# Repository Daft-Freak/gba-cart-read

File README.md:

# GBA Cartridge Reader

Hardware and software for an RP2xxx-based Game Boy and Game Boy Advance cartridge reader that presents the contents as a USB storage device.

## Board
- `board` contains the "v1" PGA2040-based GBA-only board
- `board-v4` contains the new RP2350-based design that also supports Game Boy carts and can _theoretically_ be expanded. (to be added when I make the fixed version)
- (v2/3 designs were never made. For completeness v2 added the Game Boy support, and v3 was a custom RP2040 design)

## Case

- "v1": https://www.printables.com/model/972096-gba-cartridge-reader-case

## Software
For the old RP2040-based boards, just build like any other pico-sdk based project. For the RP2350-based board configure with `cmake -DPICO_BOARD=pico2 -DPICO_RP2350A=0 [...]`.

### Tested GBA carts
 - 8K EEPROM
 - 32k SRAM
 - 64k flash
 - 128k flash

### Tested GB/GBC carts (v4)
 - No MBC
 - MBC1 (<= 512k ROM / 8k RAM)
 - MBC2
 - MBC3
 - MBC5
 - MBC7 (256 byte EEPROM)

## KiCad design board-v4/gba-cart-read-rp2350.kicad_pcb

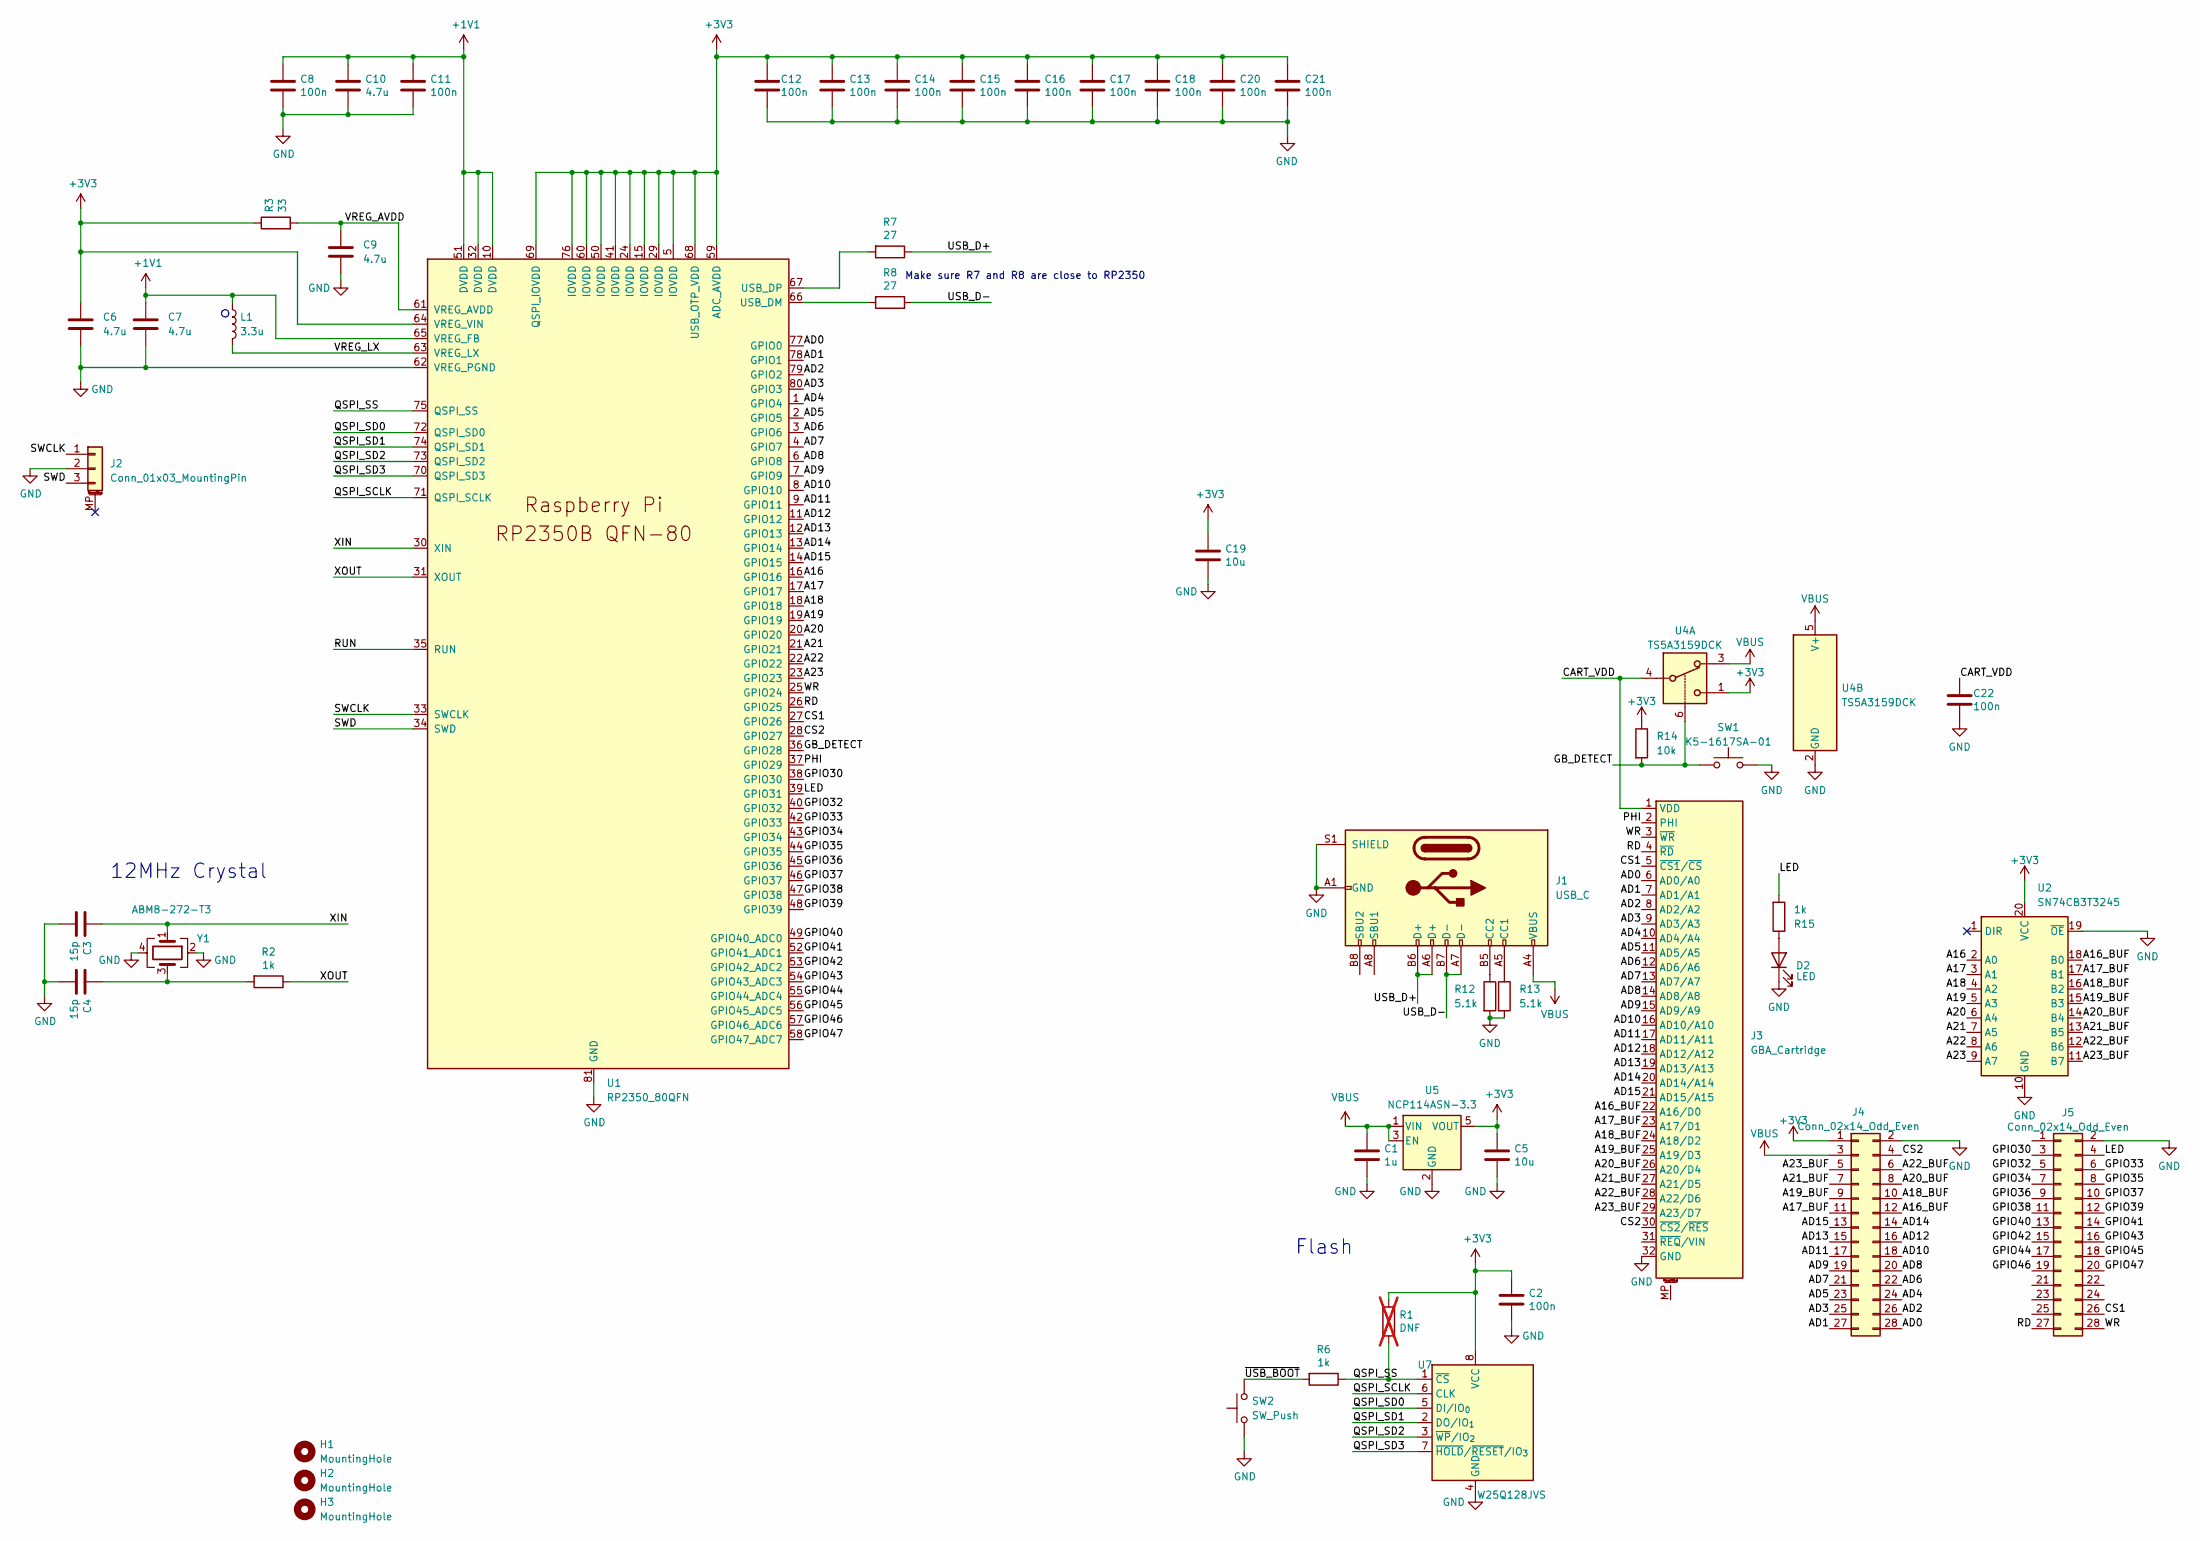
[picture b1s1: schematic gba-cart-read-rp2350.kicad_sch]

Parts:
C1: 1u; C_0805_2012Metric
C2, C8, C11, C12, C13, C14, C15, C16, C17, C18, C20, C21, C22: 100n; C_0402_1005Metric
C3, C4: 15p; C_0402_1005Metric
C5, C19: 10u; C_0805_2012Metric
C6, C7: 4.7u; C_0402_1005Metric_small_pads
C9, C10: 4.7u; C_0402_1005Metric
D2: LED; LED_0603_1608Metric
H1, H2, H3: MountingHole; MountingHole_2.7mm_M2.5
J1: USB_C; USB_C_Receptacle_HRO_TYPE-C-31-M-12
J2: Conn_01x03_MountingPin; JST_SH_SM03B-SRSS-TB_1x03-1MP_P1.00mm_Horizontal
J3: GBA_Cartridge; GameBoy_Cartridge_AGS_1x32-1MP_P1.50mm_Socket_Horizontal
J4, J5: Conn_02x14_Odd_Even; PinHeader_2x14_P2.54mm_Vertical
L1: 3.3u; L_pol_2016
R1: DNF; C_0402_1005Metric; not fitted
R2, R6, R15: 1k; R_0402_1005Metric
R3: 33; R_0402_1005Metric
R7, R8: 27; R_0402_1005Metric
R12, R13: 5.1k; R_0402_1005Metric
R14: 10k; R_0402_1005Metric
SW1: K5-1617SA-01
SW2: SW_Push; SW_Push_1P1T_XKB_TS-1187A
U1: RP2350_80QFN; RP2350-QFN-80-1EP_10x10_P0.4mm_EP3.4x3.4mm_ThermalVias
U2: SN74CB3T3245; TSSOP-20_4.4x6.5mm_P0.65mm
U4: TS5A3159DCK; SOT-363_SC-70-6
U5: NCP114ASN-3.3; TSOP-5_1.65x3.05mm_P0.95mm
U7: W25Q128JVS; SOIC-8_5.3x5.3mm_P1.27mm
Y1: ABM8-272-T3; Crystal_SMD_3225-4Pin_3.2x2.5mm

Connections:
+1V1: C7.1, C8.1, C10.1, C11.1, L1.1, U1.10 (DVDD), U1.32 (DVDD), U1.51 (DVDD), U1.65 (VREG_FB)
+3V3: C2.1, C5.1, C6.1, C12.1, C13.1, C14.1, C15.1, C16.1, C17.1, C18.1, C19.1, C20.1, C21.1, J4.1, R1.1, R3.1, R14.1, U1.5 (IOVDD), U1.15 (IOVDD), U1.24 (IOVDD), U1.29 (IOVDD), U1.41 (IOVDD), U1.50 (IOVDD), U1.59 (ADC_AVDD), U1.60 (IOVDD), U1.64 (VREG_VIN), U1.68 (USB_OTP_VDD), U1.69 (QSPI_IOVDD), U1.76 (IOVDD), U2.20 (VCC), U4.1, U5.5 (VOUT), U7.8 (VCC)
/A16: U1.16 (GPIO16), U2.2 (A0)
/A16_BUF: J3.22 (A16/D0), J4.12, U2.18 (B0)
/A17: U1.17 (GPIO17), U2.3 (A1)
/A17_BUF: J3.23 (A17/D1), J4.11, U2.17 (B1)
/A18: U1.18 (GPIO18), U2.4 (A2)
/A18_BUF: J3.24 (A18/D2), J4.10, U2.16 (B2)
/A19: U1.19 (GPIO19), U2.5 (A3)
/A19_BUF: J3.25 (A19/D3), J4.9, U2.15 (B3)
/A20: U1.20 (GPIO20), U2.6 (A4)
/A20_BUF: J3.26 (A20/D4), J4.8, U2.14 (B4)
/A21: U1.21 (GPIO21), U2.7 (A5)
/A21_BUF: J3.27 (A21/D5), J4.7, U2.13 (B5)
/A22: U1.22 (GPIO22), U2.8 (A6)
/A22_BUF: J3.28 (A22/D6), J4.6, U2.12 (B6)
/A23: U1.23 (GPIO23), U2.9 (A7)
/A23_BUF: J3.29 (A23/D7), J4.5, U2.11 (B7)
/AD0: J3.6 (AD0/A0), J4.28, U1.77 (GPIO0)
/AD1: J3.7 (AD1/A1), J4.27, U1.78 (GPIO1)
/AD2: J3.8 (AD2/A2), J4.26, U1.79 (GPIO2)
/AD3: J3.9 (AD3/A3), J4.25, U1.80 (GPIO3)
/AD4: J3.10 (AD4/A4), J4.24, U1.1 (GPIO4)
/AD5: J3.11 (AD5/A5), J4.23, U1.2 (GPIO5)
/AD6: J3.12 (AD6/A6), J4.22, U1.3 (GPIO6)
/AD7: J3.13 (AD7/A7), J4.21, U1.4 (GPIO7)
/AD8: J3.14 (AD8/A8), J4.20, U1.6 (GPIO8)
/AD9: J3.15 (AD9/A9), J4.19, U1.7 (GPIO9)
/AD10: J3.16 (AD10/A10), J4.18, U1.8 (GPIO10)
/AD11: J3.17 (AD11/A11), J4.17, U1.9 (GPIO11)
/AD12: J3.18 (AD12/A12), J4.16, U1.11 (GPIO12)
/AD13: J3.19 (AD13/A13), J4.15, U1.12 (GPIO13)
/AD14: J3.20 (AD14/A14), J4.14, U1.13 (GPIO14)
/AD15: J3.21 (AD15/A15), J4.13, U1.14 (GPIO15)
/CART_VDD: C22.1, J3.1 (VDD), U4.4
/CS1: J3.5 (~CS1/~CS), J5.26, U1.27 (GPIO26)
/CS2: J3.30 (~CS2/~RES), J4.4, U1.28 (GPIO27)
/GB_DETECT: R14.2, SW1.2, U1.36 (GPIO28), U4.6
/GPIO30: J5.3, U1.38 (GPIO30)
/GPIO32: J5.5, U1.40 (GPIO32)
/GPIO33: J5.6, U1.42 (GPIO33)
/GPIO34: J5.7, U1.43 (GPIO34)
/GPIO35: J5.8, U1.44 (GPIO35)
/GPIO36: J5.9, U1.45 (GPIO36)
/GPIO37: J5.10, U1.46 (GPIO37)
/GPIO38: J5.11, U1.47 (GPIO38)
/GPIO39: J5.12, U1.48 (GPIO39)
/GPIO40: J5.13, U1.49 (GPIO40_ADC0)
/GPIO41: J5.14, U1.52 (GPIO41_ADC1)
/GPIO42: J5.15, U1.53 (GPIO42_ADC2)
/GPIO43: J5.16, U1.54 (GPIO43_ADC3)
/GPIO44: J5.17, U1.55 (GPIO44_ADC4)
/GPIO45: J5.18, U1.56 (GPIO45_ADC5)
/GPIO46: J5.19, U1.57 (GPIO46_ADC6)
/GPIO47: J5.20, U1.58 (GPIO47_ADC7)
/LED: J5.4, R15.2, U1.39 (GPIO31)
/PHI: J3.2 (PHI), U1.37 (GPIO29)
/QSPI_SCLK: U1.71 (QSPI_SCLK), U7.6 (CLK)
/QSPI_SD0: U1.72 (QSPI_SD0), U7.5 (DI/IO_{0})
/QSPI_SD1: U1.74 (QSPI_SD1), U7.2 (DO/IO_{1})
/QSPI_SD2: U1.73 (QSPI_SD2), U7.3 (~WP/IO_{2})
/QSPI_SD3: U1.70 (QSPI_SD3), U7.7 (~HOLD/~RESET/IO_{3})
/QSPI_SS: R1.2, R6.1, U1.75 (QSPI_SS), U7.1 (~CS)
/RD: J3.4 (~RD), J5.27, U1.26 (GPIO25)
/RUN: U1.35 (RUN)
/SWCLK: J2.1, U1.33 (SWCLK)
/SWD: J2.3, U1.34 (SWD)
/USB_D+: J1.A6 (D+), J1.B6 (D+), R7.1
/USB_D-: J1.A7 (D-), J1.B7 (D-), R8.1
/VREG_AVDD: C9.1, R3.2, U1.61 (VREG_AVDD)
/VREG_LX: L1.2, U1.63 (VREG_LX)
/WR: J3.3 (~WR), J5.28, U1.25 (GPIO24)
/XIN: C3.1, U1.30 (XIN), Y1.1
/XOUT: R2.1, U1.31 (XOUT)
/~USB_BOOT: R6.2, SW2.2
GND: C1.2, C2.2, C3.2, C4.2, C5.2, C6.2, C7.2, C8.2, C9.2, C10.2, C11.2, C12.2, C13.2, C14.2, C15.2, C16.2, C17.2, C18.2, C19.2, C20.2, C21.2, C22.2, D2.1 (K), J1.A1 (GND), J1.A12 (GND), J1.B1 (GND), J1.B12 (GND), J1.S1 (SHIELD), J2.2, J3.32 (GND), J4.2, J5.2, R12.2, R13.2, SW1.1, SW2.1, U1.62 (VREG_PGND), U1.81 (GND), U2.10 (GND), U2.19 (~OE), U4.2 (GND), U5.2 (GND), U7.4 (GND), Y1.2, Y1.4
unnamed: C4.1, R2.2, Y1.3
unnamed: D2.2 (A), R15.1
unnamed: J1.A5 (CC1), R13.1
unnamed: J1.B5 (CC2), R12.1
unnamed: R8.2, U1.66 (USB_DM)
unnamed: R7.2, U1.67 (USB_DP)
VBUS: C1.1, J1.A4 (VBUS), J1.A9 (VBUS), J1.B4 (VBUS), J1.B9 (VBUS), J4.3, U4.3, U4.5 (V+), U5.1 (VIN), U5.3 (EN)

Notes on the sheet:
12MHz Crystal
Flash
Make sure R7 and R8 are close to RP2350

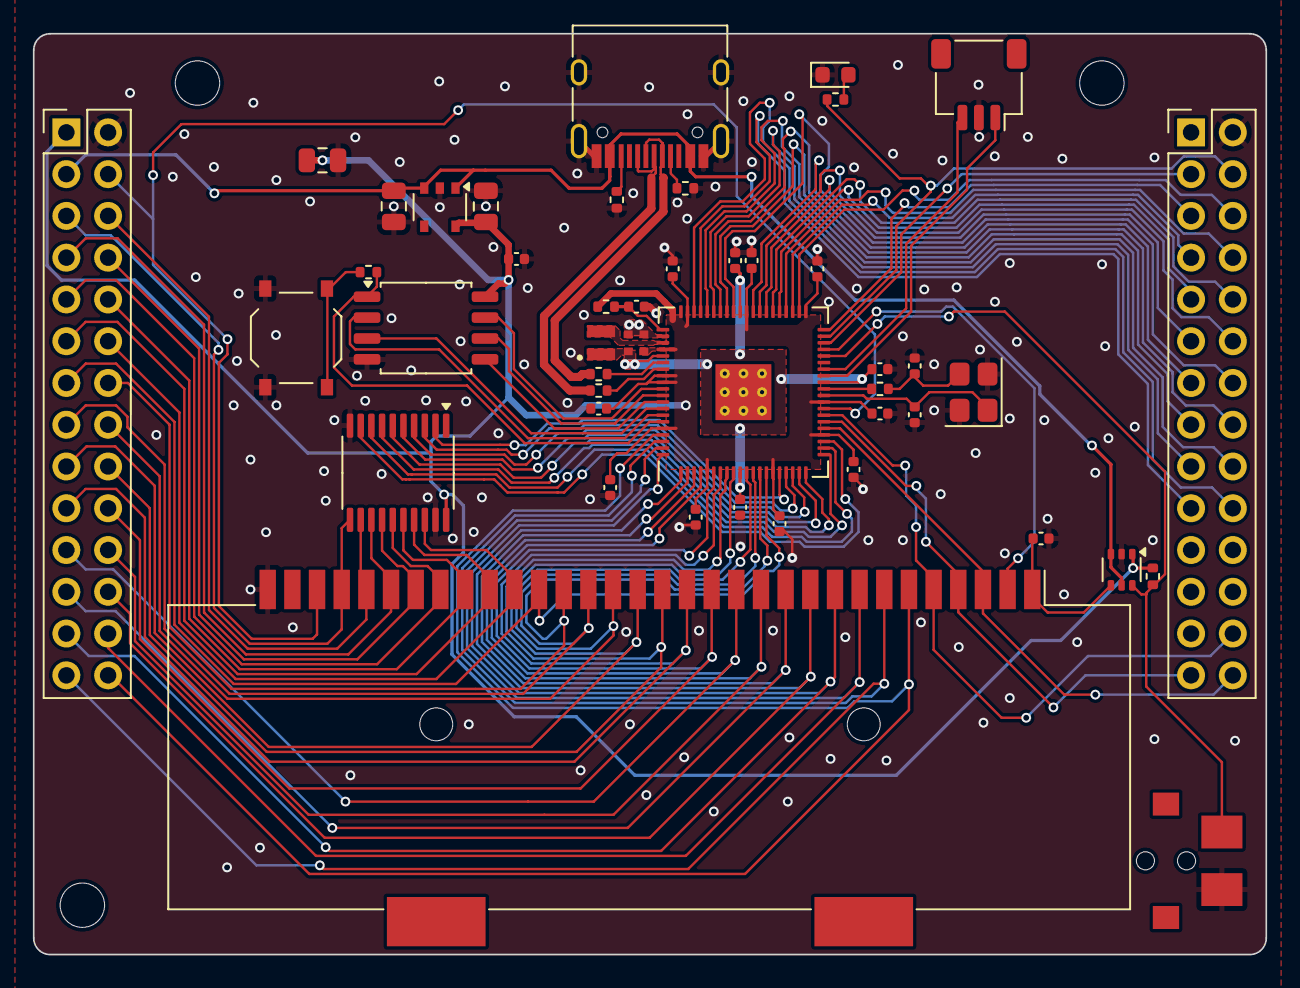
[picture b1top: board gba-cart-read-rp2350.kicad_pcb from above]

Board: 2 copper layers, 75.0 x 56.0 mm, 49 parts (0 on the bottom side), 82 nets.

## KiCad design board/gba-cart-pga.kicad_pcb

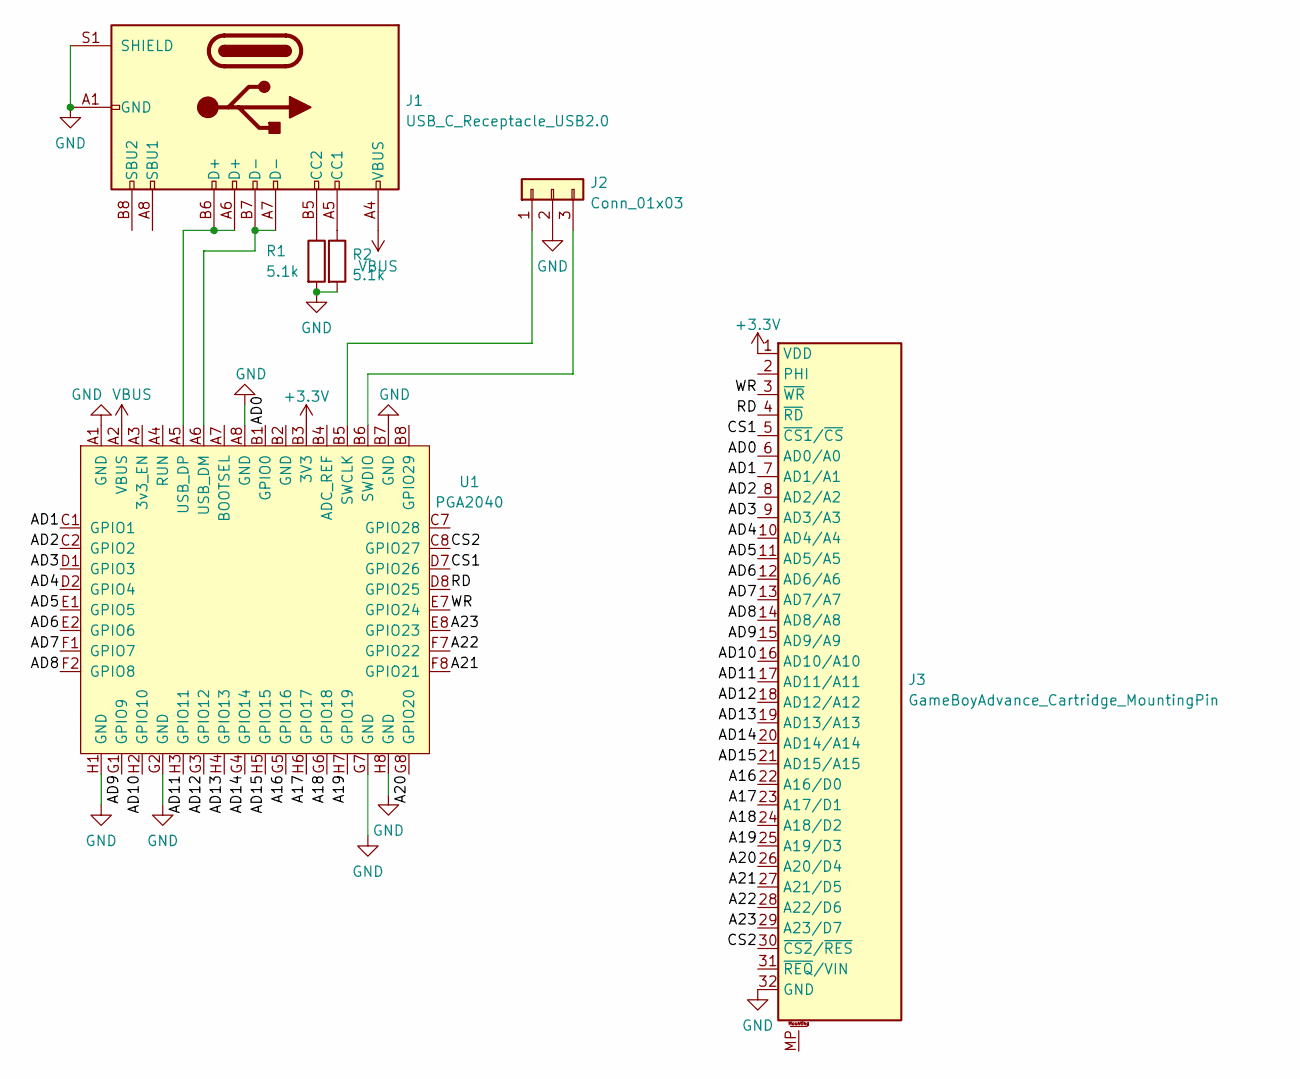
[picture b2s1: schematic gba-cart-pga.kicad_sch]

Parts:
J1: USB_C_Receptacle_USB2.0; USB_C_Receptacle_XKB_U262-16XN-4BVC11
J2: Conn_01x03; PinHeader_1x03_P2.54mm_Vertical
J3: GameBoyAdvance_Cartridge_MountingPin; GameBoy_Cartridge_AGS_1x32-1MP_P1.50mm_Socket_Horizontal
R1, R2: 5.1k; R_0805_2012Metric_Pad1.20x1.40mm_HandSolder
U1: PGA2040; PGA2040_PTH_NO_SLOT

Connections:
+3V3: J3.1 (VDD), U1.B3 (3V3)
/A16: J3.22 (A16/D0), U1.G5 (GPIO16)
/A17: J3.23 (A17/D1), U1.H6 (GPIO17)
/A18: J3.24 (A18/D2), U1.G6 (GPIO18)
/A19: J3.25 (A19/D3), U1.H7 (GPIO19)
/A20: J3.26 (A20/D4), U1.G8 (GPIO20)
/A21: J3.27 (A21/D5), U1.F8 (GPIO21)
/A22: J3.28 (A22/D6), U1.F7 (GPIO22)
/A23: J3.29 (A23/D7), U1.E8 (GPIO23)
/AD0: J3.6 (AD0/A0), U1.B1 (GPIO0)
/AD1: J3.7 (AD1/A1), U1.C1 (GPIO1)
/AD2: J3.8 (AD2/A2), U1.C2 (GPIO2)
/AD3: J3.9 (AD3/A3), U1.D1 (GPIO3)
/AD4: J3.10 (AD4/A4), U1.D2 (GPIO4)
/AD5: J3.11 (AD5/A5), U1.E1 (GPIO5)
/AD6: J3.12 (AD6/A6), U1.E2 (GPIO6)
/AD7: J3.13 (AD7/A7), U1.F1 (GPIO7)
/AD8: J3.14 (AD8/A8), U1.F2 (GPIO8)
/AD9: J3.15 (AD9/A9), U1.G1 (GPIO9)
/AD10: J3.16 (AD10/A10), U1.H2 (GPIO10)
/AD11: J3.17 (AD11/A11), U1.H3 (GPIO11)
/AD12: J3.18 (AD12/A12), U1.G3 (GPIO12)
/AD13: J3.19 (AD13/A13), U1.H4 (GPIO13)
/AD14: J3.20 (AD14/A14), U1.G4 (GPIO14)
/AD15: J3.21 (AD15/A15), U1.H5 (GPIO15)
/CS1: J3.5 (~CS1/~CS), U1.D7 (GPIO26)
/CS2: J3.30 (~CS2/~RES), U1.C8 (GPIO27)
/RD: J3.4 (~RD), U1.D8 (GPIO25)
/WR: J3.3 (~WR), U1.E7 (GPIO24)
GND: J1.A1 (GND), J1.A12 (GND), J1.B1 (GND), J1.B12 (GND), J1.S1 (SHIELD), J2.2, J3.32 (GND), R1.2, R2.2, U1.A1 (GND), U1.A8 (GND), U1.B7 (GND), U1.G2 (GND), U1.G7 (GND), U1.H1 (GND), U1.H8 (GND)
unnamed: J1.A5 (CC1), R2.1
unnamed: J1.A6 (D+), J1.B6 (D+), U1.A5 (USB_DP)
unnamed: J1.A7 (D-), J1.B7 (D-), U1.A6 (USB_DM)
unnamed: J1.B5 (CC2), R1.1
unnamed: J2.1, U1.B5 (SWCLK)
unnamed: J2.3, U1.B6 (SWDIO)
VBUS: J1.A4 (VBUS), J1.A9 (VBUS), J1.B4 (VBUS), J1.B9 (VBUS), U1.A2 (VBUS)

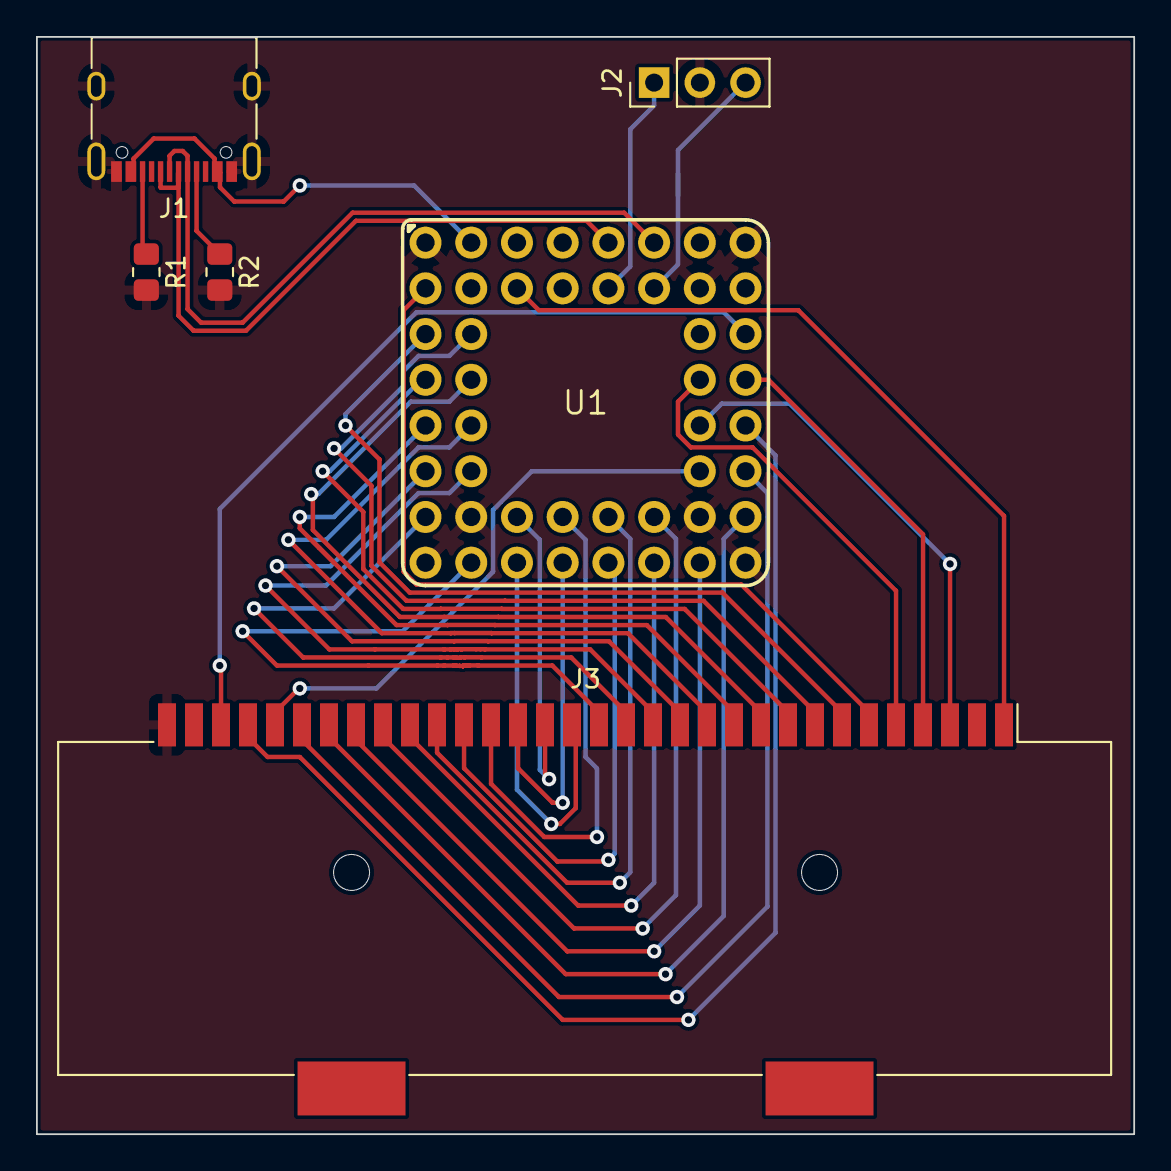
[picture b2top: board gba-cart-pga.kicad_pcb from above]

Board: 2 copper layers, 61.0 x 61.0 mm, 6 parts (0 on the bottom side), 37 nets.

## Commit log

2022-06-15 Initial commit
    Reads cart as a block device at ~340kB/s. USB code borrowed from 32blit-sdk.
2022-06-15 Break code up and move stuff around
2022-06-15 PIO cart reading
    Now up to 511 kB/s
2022-06-15 Increase MSC buffer size
    ~813 kB/s
2022-06-15 Return false for writable
2022-06-15 Emulate a filesystem with a rom file
    There's still a lot of hardcoding in here... but it works
2022-06-15 Enable some warnings
2022-06-15 Add function for setting FS data size
    ... and another to get the right sector count for the USB code
2022-06-15 Basic checksum and size check
2022-06-16 Helper for reading header/checksum check
    Read a few fields while we're here
2022-06-16 Move ROM size calc
2022-06-16 Don't attempt to calc FS sectors for no data
2022-06-16 Return not ready/no media for empty FS
2022-06-16 Cart detection polling
2022-06-16 Rework FS to handle multiple files
    ... and allow names
2022-06-16 Check if game code has changed before recalculating everything
2022-06-16 Set game code as filename
    Title is a bit long, and we don't yet do LFNs
2022-06-16 Round up sectors to cluster size
2022-06-16 Pass a callback for file reads
    Now we can _really_ handle multiple files... and the FS code doesn't need to see the cart code
2022-06-16 Fix the 64k range assert
2022-06-16 Basic code for reading RAM saves
2022-06-16 Attempt save type detection
2022-06-16 Allow reading RAM saves
    Seems to work
2022-06-16 Allow reading 64K flash saves
    This just works (helps if you don't test with a broken emulator)
2022-06-16 Handle 128K flash saves
    Requires writes for bank switching
2022-06-16 Rename copy/pasted function
2022-06-17 EEPROM save reading
    512 bytes is entirely untested
2022-06-18 Don't add an extra cluster if already aligned
2022-06-18 Warning fix
2022-06-18 Enable PIO when it's used
    Instead of disabling it when it isn't
2022-06-18 Optimise PIO program
    Avoid nops for sideset, pack address/count, push values for dir changes and enable autopull
    13 -> 6 instructions
2022-06-18 Fix the range assert more
2022-06-18 Split ROM reads if the address would wrap
2022-06-18 Handle multiple sector reads in the FS code
    At least for files, doesn't make it any faster... but seems less bad
2022-06-18 Avoid recalculating offsets every read
2022-06-18 Don't assign RAM CS to PIO
    It's not used and probably won't be. This also means we're not using all of the sideset bits
2022-06-18 Less speed, more stable
2022-06-20 Rename PIO program to the thing it does (ROM reads)
2022-06-20 Reorder PIO setup
    Push data before clearing the stall flag and enabling.
2022-06-20 Shift the other way
    No, the other right... (More copy/paste that wasn't helping here)
2022-06-20 Use DMA for rom reads
    Avoids stalling at a bad time and allows reducing the clock div again (not that it improves much over USB...)
2022-06-20 PIO for EEPROM reads
    Mostly to see if I could
2022-06-21 Use DMA bswap
    Uh, I forgot this was a thing
2022-06-21 Optimise SRAM access a bit
2022-06-22 WIP code for DMG carts
    Don't have the right hw to do this properly (no detection or voltage switching)
2022-07-10 Add PCB
2023-10-04 gitignore for pcb
2023-10-04 Tweak so that stdio_usb works
2023-10-04 Remove custon debug printint
2023-10-04 Avoid getting stuck in an insert/remove loop when cart doesn't change
    How long has this been broken?
2023-10-04 Set CS low after writing address, not at the same time
2023-10-04 Add an additional check to getROMSize
    Checking for floating values is not so reliable...
2023-10-04 Sprinkle some extra volatile on things
    Trying to fix most of getSaveType being optimised out... this doesn't do it
2023-10-04 Add some memory barriers to getSaveType
    ... and I have save detection again!
2023-10-04 Try not to break USB while scanning for save type
2023-10-04 Clean up unused CDC write code
2023-10-04 Wait for mount before doing anything
    The save scan is still too slow to be doing during enumeration
2024-01-03 More delay from CS low to RD low, set address before CS low for EEPROM too
    At least for N4/3 there are always two cycles after CS low
2024-01-03 Run ROM reads as fast as possible, slow down for EEPROM (slightly less)
2025-07-01 Some LED blinking for the new board
2025-07-01 Use GB cart detection pin for the new board
    It still doesn't work though
2025-07-02 Buffer direction hackery for the new board
    Using RD directly to control direction didin't seem to work, so I cut it and now we're only using the "override"
2025-07-02 Avoid repeatedly adding and removing gameboy cart
2025-07-02 Rename some GBA header reading bits
2025-07-02 More DMG header reading
2025-07-02 Use the title from the header for DMG
2025-07-02 Rename GBA ROM size helper
2025-07-02 More helpers for DMG RAM/ROM sizes
    Not handling banking yet so not that useful
2025-07-02 Add MBC type helper
    Mostly copied from DaftBoy
2025-07-02 Add code for reading MBC1 ROM
2025-07-02 Wire up MBC1 ROM reading
2025-07-02 Use appropriate file extension for CGB compatible carts
2025-07-02 Add some basic support for reading MBC1 RAM
    The cart I have only has 8K RAM...
2025-07-02 Wire up RAM for DMG carts
2025-07-03 MBC3 reading support
2025-07-03 Add LFN support to filesystem
    Could improve this my not requiring both names to be passed, but this works
2025-07-03 Use long names for ROM/SAV files
    No more "TETRIS D" or "POKEMON_"
2025-07-03 Skip LFN entries when iterating
    Fixes some brokenness
2025-07-04 Pad LFN entries with FFFF
    Now it works on windows
2025-07-04 Add helper to generate short name from long name
2025-07-04 Use new helper
    This does change the behaviour for GBA, but... less repetition
2025-07-05 Add MBC5 reading
    Getting a bit duplicated, but not done yet...
2025-07-05 Wire up MBC5
2025-07-05 README
2025-07-05 Add install stop
2025-07-05 Add build action
2025-07-10 gAdd some more delays to GBA RAM writing to (hopefully) fix reading 128k flash
2025-07-10 Add MBC2 read helpers
2025-07-10 Force RAM size to 512 for MBC2
2025-07-10 Wire up MBC2 reading
2025-07-10 Add MBC2 to readme
2025-07-11 Do MBC RAM banck switching before enabling RAM
    This feels safer
2025-07-11 Be more careful in writeDMG
    Doesn't fix the save corruption problems, but also doesn't hurt?
2025-07-12 Move IO init as early as possible
    Seems to be safer for not corrupting saves, so long as the cartridge is connected before power...
2025-07-13 Adjyst clock div for RP2350
    It runs at 150MHz by default
2025-07-13 DMG CS is only for RAM
    How did this take so long to figure out?
2025-07-13 Allow specifying the volume label in the filesystem code
2025-07-13 Revert one of the delays in writeDMG
    Not that the CS stuff is fixed
2025-07-14 Add helper for PIO program switch
2025-07-14 Avoid redundant program changes
    Probably not a massive performance concern but still
2025-07-14 Use a PIO program for RAM/DMG ROM reads
    An improvement on the manual PIO exec stuff at least
2025-07-15 Add MBC7 detection
2025-07-15 Add MBC7 ROM read helper
    The same as MBC3
2025-07-15 Add MBC7 EEPROM read helper
2025-07-15 Force MBC7 "RAM" size
2025-07-15 Wire up MBC7
2025-07-15 Refactor MBCn handling
    It's mostly just different size banking registers
2025-07-19 Copy first four chars of DMG title to curGameCode
    It's at least better than what we were doing before
2025-07-19 Add a dummy read before writing MBC5 high bank num
2026-01-01 Add the V4 board files
    I already listed them in the readme. Note that this is the revised bersion that doesn't need DIR_OVERRIDE_PIN
